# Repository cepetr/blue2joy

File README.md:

# 🕹️ Blue2Joy

**Blue2Joy** is an adapter that lets you use modern Bluetooth controllers with Atari 8-bit computers. It emulates **digital joysticks**, **analog paddles**, and supports **bidirectional communication** and much more. Try the live demo: https://cepetr.github.io/blue2joy/main.

While primarily intended for gamepads, the device is not limited to them - in principle, any BLE HID device, such as a keyboard or mouse, can be connected.

> Only devices that fully support the BLE HID over GATT Profile (HOGP) are supported. For this reason many older devices (especially gamepads) are unfortunately not usable with Blue2Joy. See [compatible devices](/doc/compatible-devices.md).

<div>

</div>

<div>

</div>

## Have a look at some demos:

## Use Cases
While there are other adapters that let Bluetooth controllers act as digital joysticks, Blue2Joy goes further. Besides standard and expected use cases, there are a few new possible ones that utilize analog input emulation or bidirectional communication:

- Use a gamepad as a digital joystick with up to 3 buttons (Joy2B+ standard)
- Use gamepad's analog sticks as paddles (direct or integration mode)
- Emulate paddles with a mouse
- Use a gamepad as an analog joystick (two axes on analog inputs) with up to 5 buttons
- Connect a mouse digitally- using quadrature encoding as on the Atari ST
- Connect a mouse in an analog way - using analog inputs for deltas, with up to 5 buttons
- Configure Blue2Joy via SPI-like communication over the joystick port
- Emulate the Y-axis of a light pen (conceptual idea, not sure if possible)
- Emulate an XEP80 terminal (work in progress)
- Send keycodes from the browser to Atari via paddle lines (used by the XEP80 terminal; requires [btjkbd.sys](/kbdrv/)).

Although designed for Atari 8-bit systems, Blue2Joy can be used with any device that follows the same joystick port pinout - with paddle functionality available only on Atari computers (see [details](/doc/paddle-emulation.md)).

## 🚧 Project Status

Blue2Joy is currently under active (but really slow) development. The hardware is stable and most of the core features have been successfully tested, but the software still needs some work to reach the level of polish I would consider complete.

## Repository Structure

This repository contains complete project documentation and source code for all Blue2Joy components shown in the following image.

### Blue2Joy Hardware
- Nordic nRF52840 (Cortex-M4F @ 64 MHz) with integrated Bluetooth 5 LE radio
- USB 2.0 Full-Speed (device mode only) for firmware updates, debugging, or use as a faster alternative to Bluetooth
- Female 9-pin D-sub connector
- RGB LED used as a status indicator (see [details](/doc/state-signalling.md))
- Two user push-buttons (see [details](/doc/button-functions.md))

For more details, see the [hardware](/hardware/) folder.

### Blue2Joy Firmware
- Supports pairing and connection to BLE HID devices (tested with Xbox Wireless Controller)
- Emulates a joystick port digital inputs as well as analog paddle potentiometers
- Supports bidirectional (SPI) communication with the Atari
- Indicates device status with an RGB LED
- Allows custom mapping of HID-device controls to joystick and paddle inputs
- Emulates an XEP80 terminal

For more details, see the [firmware](/firmware/) folder.

### Web Configuration
- A web application that allows you to configure the Blue2Joy device directly from any browser supporting the Web Bluetooth or Web USB standards
- Provides an easy way to configure the mapping of HID controls to joystick port digital and analog pins
- Allows you to configure the device even while it is connected to HID devices (e.g., gamepads, mice)
- Emulates an XEP80 terminal

The application is available at https://cepetr.github.io/blue2joy/main.

For more details, see the [webconfig](/webconfig/) folder.

### Atari Blue2Joy Keyboard driver
A driver for SpartaDOS that lets you use Blue2Joy as a keyboard. It can be used together with
XEP80 or on its own.

For more details, see the [atari](/atari/btjkbd) folder.

### Atari Blue2Joy Configuration Application
- Not implemented yet. This component currently exists only as a design intention.
- Intended to be an application that allows configuring the Blue2Joy device directly from Atari
- Planned to use the bidirectional (SPI-like) communication over the joystick port

For more details, see the [atari](/atari/btjmenu) folder.

## Feedback & Contributions

I'd be very happy to receive any feedback, pull requests, or even just a note that you've built and tried out Blue2Joy.

## License

This repository contains software, firmware, and hardware design files.

### Software and Firmware

All software and firmware files (in `atari/`, `firmware/` and `webconfig/`) are licensed under the GNU General Public License, version 3.

See [LICENSE-GPL](LICENSE-GPL) for details.

### Hardware

Schematics, PCB layout, mechanical design files (in `hardware/`) are licensed under the CERN Open Hardware Licence Version 2 - Strongly Reciprocal. You are free to use, modify, and share them, but if you distribute hardware or modified design files, you must also share your changes under the same license.

See [LICENSE-CERN](LICENSE-CERN) for details.

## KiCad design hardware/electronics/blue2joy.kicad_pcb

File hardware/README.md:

# 🔧 Blue2Joy — hardware

This folder contains the **KiCad** project and 3D design files for the Blue2Joy adapter:

* [`electronics/`](/hardware/electronics/) - KiCad project
* [`mechanical/`](/hardware/mechanical/) - 3-D model of the device’s enclosure

## Schematic & BOM

The design uses readily available SMD components and a XIAO nRF52840 module to keep the total cost and assembly complexity relatively low.

Schematic in PDF format is available [here](/hardware/electronics/fab_v1e/blue2joy-v1e.pdf)

The estimated parts cost is roughly USD 25, depending on the supplier and any volume discounts.

| # | Qty| Reference | Package |Part Numbers |
|----|---|-----------|---------|--------------------|
| 1  | 1 | U1 | | XIAO nRF52840 Plus |
| 2  | 1 | U2 | SOT-23-5 | TPS73133DBV |
| 3  | 2 | U3, U5 | SOT-23-6 | 74LVC2G17DBV |
| 4  | 3 | U4, U7, U8 | SOT-23-6 | 74LVC2G07DBV |
| 5  | 1 | U6 | SOT-23-5 | TLV9001IDBV |
| 6  | 1 | U9 | SOT-23-5 | XC8110AA01MR |
| 7  | 1 | U10 | SOT-23-6 | 74HCT2G34GV |
| 8  | 2 | Q1, Q3 | SOT-23-3 | BSS138 |
| 9  | 2 | Q4, Q5 | SOT-23-3 | SI2323DDS |
| 10 | 1 | J1 | - | DE9 Socket (Male)  |
| 11 | 2 | SW1, SW2 | - | OMRON B3FS-1010 |
| 12 | 1 | D1 | 2020 | WS2812-2020 |
| 13 | 8 | R1, R2, R3, R13, R14, R15, R18, R19 | 0805 | 10kΩ/125mW |
| 14 | 2 | R6, R10 | 0805 | 100kΩ/125mW |
| 15 | 4 | R8, R9, R11, R12 | 0805 | 18kΩ/125mW |
| 16 | 5 | R20, R21, R22, R23, R24 | 0805 | 820Ω/125mW |
| 17 | 2 | R4, R17 | 0805 | 1.8kΩ/125mW |
| 18 | 2 | R5, R16 | 0805 | 2.2kΩ/125mW |
| 19 | 4 | C1, C2, C3, C4 | 0805 | 1µF |
| 20 | 1 | C5 | 0805 | 10µF |
| 21 | 3 | C6, C7, C8 | 0805 | 100nF |

## PCB

The [`electronics/fab_v1d`](/hardware/electronics/fab_v1d/) folder contains the manufacturing files for the latest PCB revision.

## Assembly notes

Building the board **does require basic SMT soldering skills**.
If you have never worked with solder paste or hot air before, expect a small learning curve - nothing close to rocket science, but still a step up from through-hole work.

| Part type | Package | Difficulty (subjective) |
|-----------|---------|------------|
| Passives  | **0805** | easy; forgiving |
| Logic & power | **SOT-23-x** | fine for hot-air or drag solder, **be extra careful with orientation - SOT-23-6 parts have a tiny, barely visible dot marking pin 1** |
| MCU module | **XIAO nRF52840 Plus** (castellated) | can be hand-soldered with a fine-tip iron |
| RGB LED | **WS2812C-Mini** | the smallest part; watch orientation |

After assembly, verify that there are no shorts between pins on the SOT-23-x packages.

## DE9 Socket

DE9 (Cannon) connectors are manufactured only with a metal housing. After cutting along the edge, the plastic part can be popped out like a nut. However, the plastic parts differ between manufacturers, and in some cases, they need to be glued together.

## Hardware Status & Disclaimer

Although the device has been tested with three Atari models (800XL, 800XE, and 600XL - all PAL), hidden design flaws may still exist. Use all design files, instructions, and the board at your own risk; no warranties or guarantees are implied.

The plastic parts were printed from PLA (standard 0.4 mm nozzle, 0.2 mm layer height, 30% infill) on a Prusa Mk3 printer. The tolerances are quite tight, so it’s likely that on a different printer or with another material, there may be issues fitting the parts together.

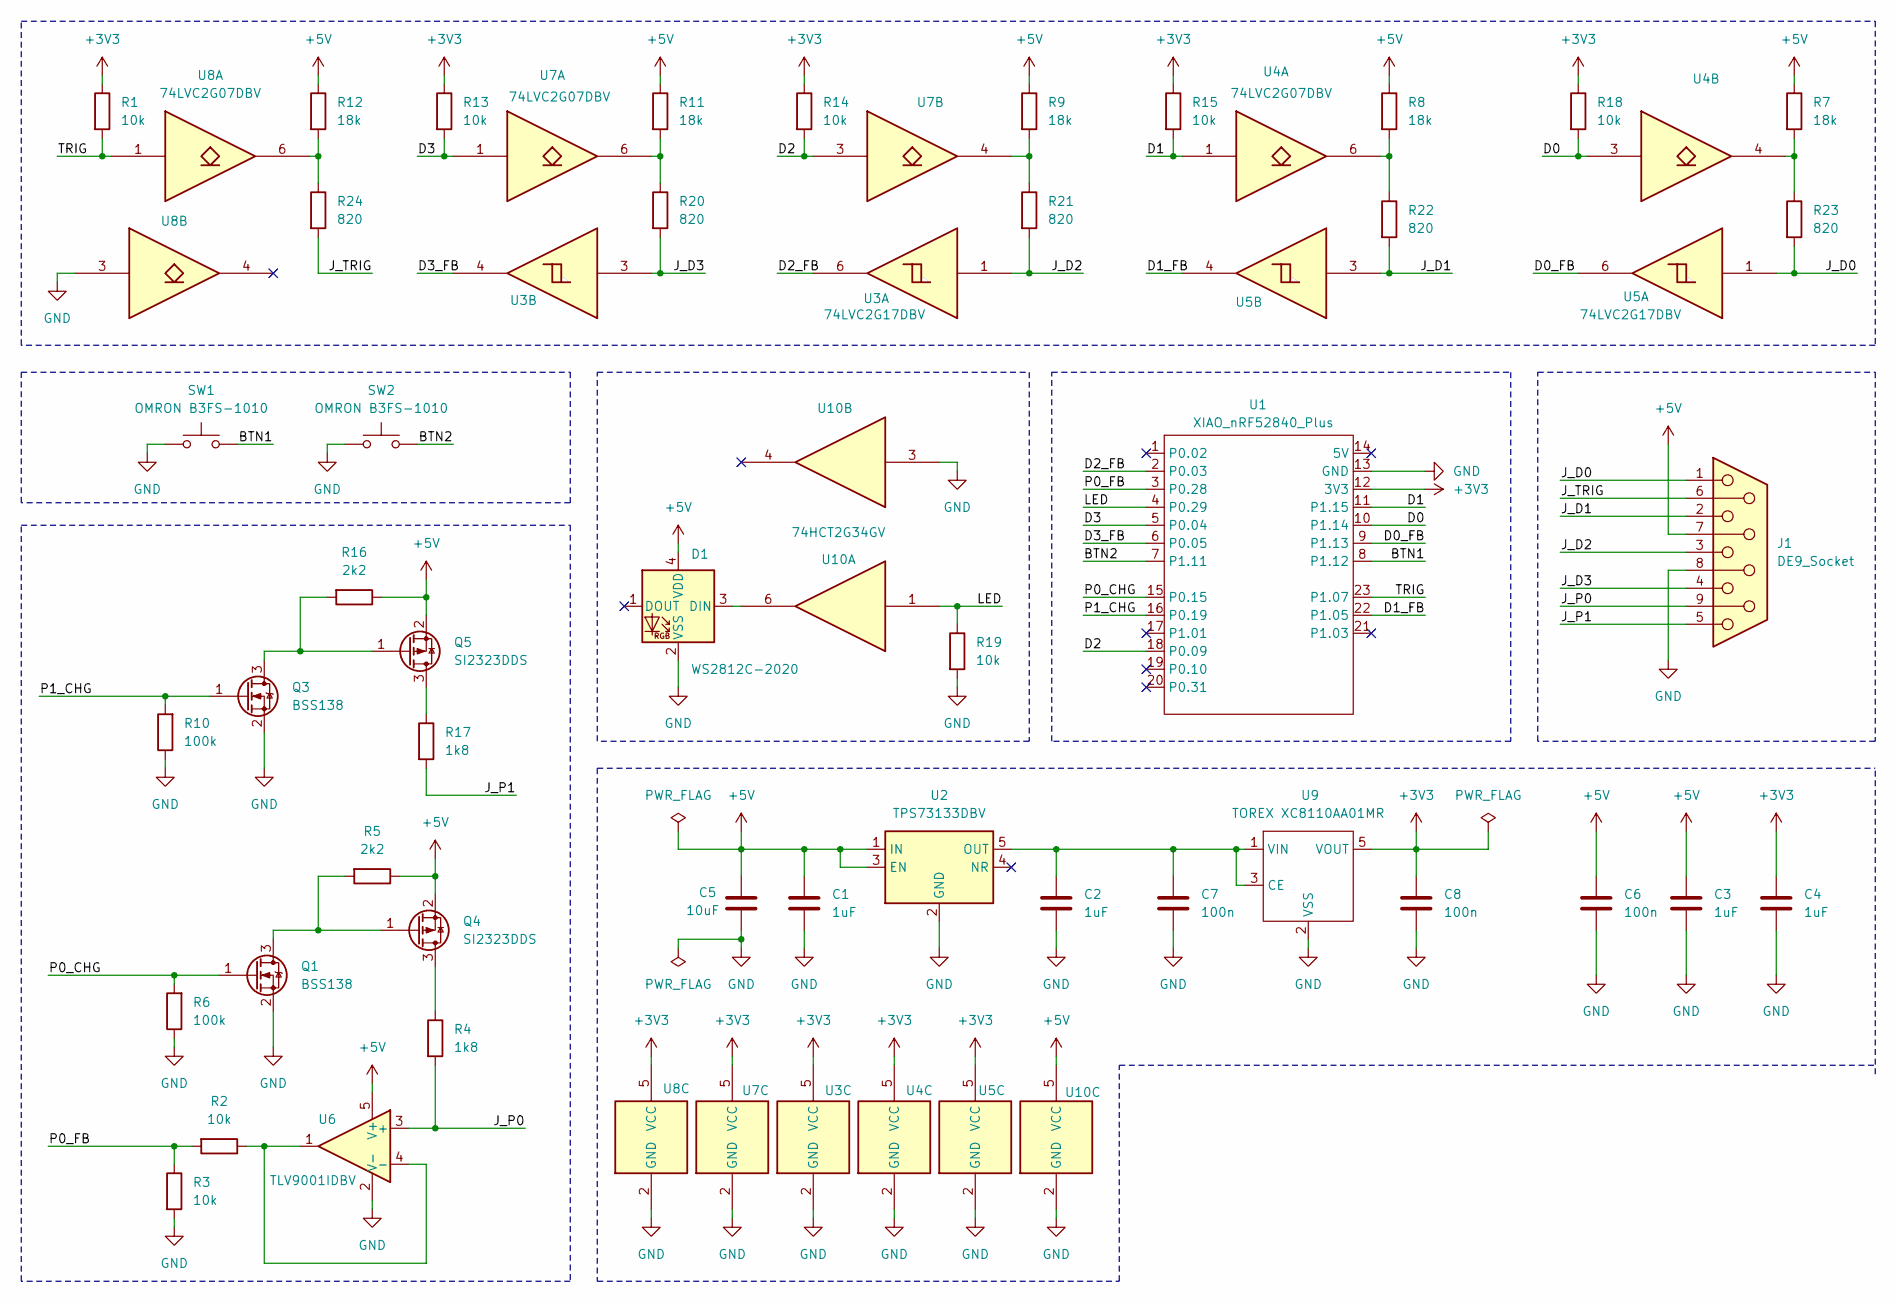
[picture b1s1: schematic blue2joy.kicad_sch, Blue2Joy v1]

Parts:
C1, C2, C3, C4: 1uF; C_0805_2012Metric
C5: 10uF; C_0805_2012Metric
C6, C7, C8: 100n; C_0805_2012Metric
D1: WS2812C-2020; LED_WS2812B-2020_PLCC4_2.0x2.0mm
J1: DE9_Socket; DSUB-9_Socket_EdgeMount_P2.77mm
Q1, Q3: BSS138; SOT-23
Q4, Q5: SI2323DDS; SOT-23
R1, R2, R3, R13, R14, R15, R18, R19: 10k; R_0805_2012Metric
R4, R17: 1k8; R_0805_2012Metric
R5, R16: 2k2; R_0805_2012Metric
R6, R10: 100k; R_0805_2012Metric
R7, R8, R9, R11, R12: 18k; R_0805_2012Metric
R20, R21, R22, R23, R24: 820; R_0805_2012Metric
SW1, SW2: OMRON B3FS-1010; SW_SPST_Omron_B3FS-100xP
U1: XIAO_nRF52840_Plus; XIAO-nRF52840-Plus-SMD
U2: TPS73133DBV; SOT-23-5
U3, U5: 74LVC2G17DBV; SOT-23-6
U4, U7, U8: 74LVC2G07DBV; SOT-23-6
U6: TLV9001IDBV; SOT-23-5
U9: TOREX XC8110AA01MR; SOT-23-5
U10: 74HCT2G34GV; SOT-23-6

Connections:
+3V3: C4.1, C8.1, R1.1, R13.1, R14.1, R15.1, R18.1, U1.12 (3V3), U3.5 (VCC), U4.5 (VCC), U5.5 (VCC), U7.5 (VCC), U8.5 (VCC), U9.5 (VOUT)
+5V: C1.1, C3.1, C5.1, C6.1, D1.4 (VDD), J1.7, Q4.2 (S), Q5.2 (S), R5.1, R7.1, R8.1, R9.1, R11.1, R12.1, R16.1, U2.1 (IN), U2.3 (EN), U6.5 (V+), U10.5 (VCC)
/BTN1: SW1.1, U1.8 (P1.12)
/BTN2: SW2.2, U1.7 (P1.11)
/D0: R18.2, U1.10 (P1.14), U4.3
/D0_FB: U1.9 (P1.13), U5.6
/D1: R15.2, U1.11 (P1.15), U4.1
/D1_FB: U1.22 (P1.05), U5.4
/D2: R14.2, U1.18 (P0.09), U7.3
/D2_FB: U1.2 (P0.03), U3.6
/D3: R13.2, U1.5 (P0.04), U7.1
/D3_FB: U1.6 (P0.05), U3.4
/J_D0: J1.1, R23.2, U5.1
/J_D1: J1.2, R22.2, U5.3
/J_D2: J1.3, R21.2, U3.1
/J_D3: J1.4, R20.2, U3.3
/J_P0: J1.9, R4.2, U6.3 (+)
/J_P1: J1.5, R17.2
/J_TRIG: J1.6, R24.2
/LED: R19.1, U1.4 (P0.29), U10.1
/P0_CHG: Q1.1 (G), R6.2, U1.15 (P0.15)
/P0_FB: R2.2, R3.1, U1.3 (P0.28)
/P1_CHG: Q3.1 (G), R10.2, U1.16 (P0.19)
/TRIG: R1.2, U1.23 (P1.07), U8.1
GND: C1.2, C2.2, C3.2, C4.2, C5.2, C6.2, C7.2, C8.2, D1.2 (VSS), J1.8, Q1.2 (S), Q3.2 (S), R3.2, R6.1, R10.1, R19.2, SW1.2, SW2.1, U1.13 (GND), U2.2 (GND), U3.2 (GND), U4.2 (GND), U5.2 (GND), U6.2 (V-), U7.2 (GND), U8.2 (GND), U8.3, U9.2 (VSS), U10.2 (GND), U10.3
unnamed: D1.3 (DIN), U10.6
unnamed: Q1.3 (D), Q4.1 (G), R5.2
unnamed: Q3.3 (D), Q5.1 (G), R16.2
unnamed: Q4.3 (D), R4.1
unnamed: Q5.3 (D), R17.1
unnamed: R11.2, R20.1, U7.6
unnamed: R12.2, R24.1, U8.6
unnamed: R9.2, R21.1, U7.4
unnamed: R8.2, R22.1, U4.6
unnamed: R7.2, R23.1, U4.4
unnamed: C2.1, C7.1, U2.5 (OUT), U9.1 (VIN), U9.3 (CE)
unnamed: R2.1, U6.1, U6.4 (-)

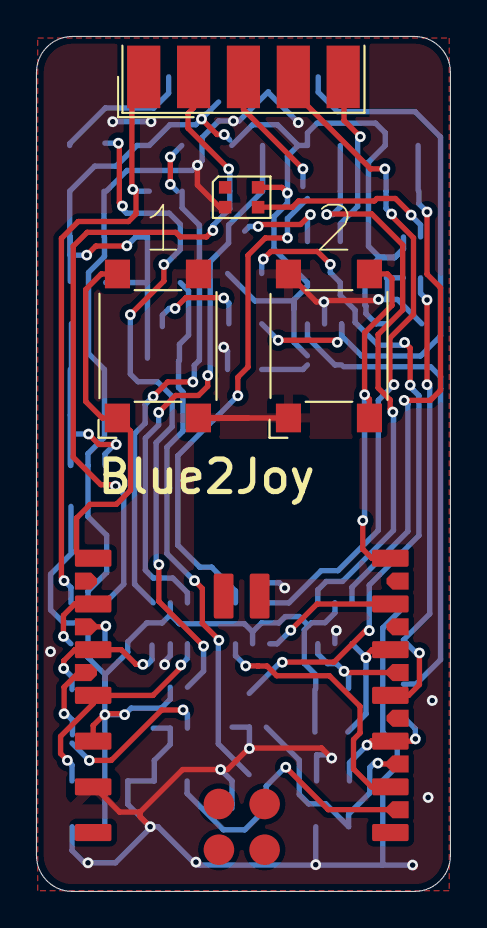
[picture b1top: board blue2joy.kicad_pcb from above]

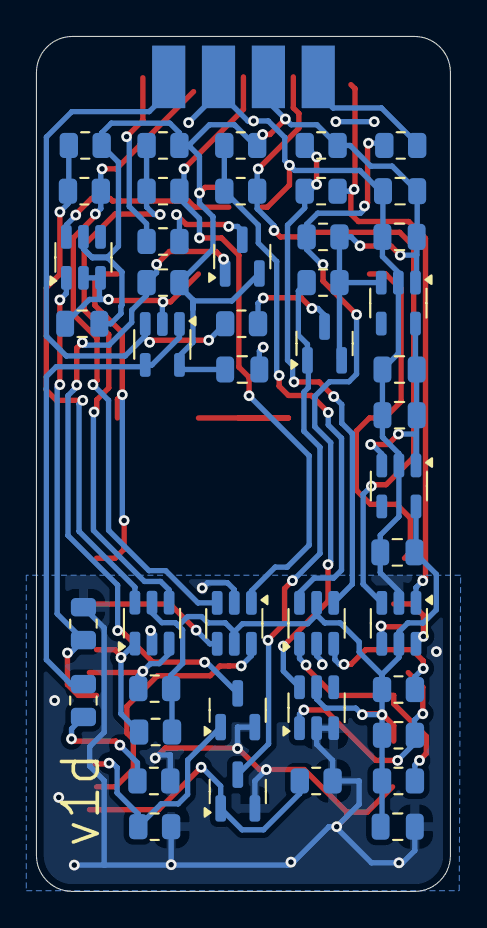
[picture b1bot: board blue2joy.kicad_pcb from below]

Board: 2 copper layers, 23.0 x 47.5 mm, 50 parts (45 on the bottom side), 37 nets.

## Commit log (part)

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2025-10-25 remove bonded flag
2025-10-25 show connection state string
2025-10-25 fix scan dialog button
2025-10-25 fix txq_ready flag handling
2025-10-25 Add profile change, device delete
2025-10-25 Add connect button
2025-10-25 add hatSwitch, intSpeed configuration
2025-10-25 fix fixed profile
2025-10-25 fix code formatting
2025-10-25 update todo
2025-10-25 reorganize files
2025-10-25 add sidebar nav
2025-10-25 group pins and pots
2025-10-26 replace picocss with bootstrap
2025-10-26 refactor pin and pot editors
2025-10-26 remove unnecessary comments
2025-10-26 one line editors
2025-10-26 pin/pot header of the left
2025-10-26 simplify pin/pot editors
2025-10-26 add Not Assigned usage
2025-10-26 improve pot editor
2025-10-28 detect disconnected device
2025-10-28 update todos
2025-10-28 add start/stop advertising button
2025-10-28 refactor btsvc, make is_advertising atomic
2025-10-28 add advertising timeout
2025-10-28 center home screen
2025-10-28 update 3d files
2025-10-30 configure rc oscillator calibration
2025-10-30 estimate pot scanning period
2025-10-30 minor doc updates
2025-11-15 centralize device scanning logic in BtjModel
2025-11-15 improve error handling
2025-11-15 add list of compatible devices
2026-01-10 improve navigation, add offcanvas menu
2026-01-10 improve pin/pot editor layout
2026-01-10 subscribe to the first report in the report map
2026-01-10 update the list of compatible devices
2026-01-10 discover report characteristics properly
2026-01-11 update doc
2026-01-11 Deploy webconfig for refs/heads/dev 83e64820c5a60210d097cd2bc1a51690986f0b69
2026-01-11 Deploy webconfig for refs/heads/main 7cfd7e5f635778ab4421fdfd35b870682fe4e947
2026-01-11 Deploy webconfig for refs/tags/v0.1 7cfd7e5f635778ab4421fdfd35b870682fe4e947
2026-01-11 Deploy webconfig for refs/heads/dev f3997a750e14e0e93c379cd23fa59fcdc3536843
2026-01-11 Deploy webconfig for refs/heads/dev de0f1742ecac871c870539c2e86fbb9555068cc0
2026-01-11 fix routing when using version prefix
2026-01-17 use constants for pot min/max values
2026-01-17 improve mapper, introduce integrators, analog encoders
2026-01-17 reconfigure io pins if the active profile is modified
2026-01-18 fix hid usage selector
2026-01-18 update documentation
2026-01-20 improve responsiveness on smaller screens
2026-01-20 improve html formatting
2026-01-21 implement event handler as arrow functions
2026-01-21 use hash based routing
2026-01-22 decrease padding and margin in editor cards
2026-01-23 refactor filtering logic in hid-usage-select
2026-01-23 indicate the device state using icons
2026-01-24 Deploy webconfig for refs/heads/main c044f10ed8133ad798e0c5b402b8f7d3912fa732
2026-01-24 docs: introduce new todo list
2026-01-24 display digital I/O and potentiometer states in web UI
2026-01-24 Deploy webconfig for refs/heads/main 1341ea238d3ab0ff4edbc8877fbeef8f62b088e6
2026-01-24 fix: close off-canvas navbar on menu item selection
2026-01-24 Deploy webconfig for refs/heads/main 8b34d09968044fce412b47f3ab97f2809fad9546
2026-01-24 Deploy webconfig for refs/tags/v0.2 fdede7f2eb40641e44b04d57845cf0318c1d1324
2026-01-24 fix: change navbar to fixed position
2026-01-25 fix: update pot outputs when mapped to integrators
2026-01-25 feat: improve pot accuracy and decrease jitter
2026-01-26 docs: add link to youtube video
2026-02-07 Deploy webconfig for refs/heads/dev 37e24393fac06f7e3561e95dac261e45ec6e61c9
2026-02-15 Deploy webconfig for refs/heads/dev d2f2fb405a16679e680dbffca6a3e6028b5e1cf0
2026-02-15 Deploy webconfig for refs/heads/dev 2f0d46f78eb7f1efc6667cf7629ddd15d8cb884f
2026-02-16 refactor: introduce joy_port module
2026-02-22 Deploy webconfig for refs/heads/dev adc2743a07af16aeb9920ea52470f24ef194586f
2026-02-28 fix: get rid of compiler warning
2026-02-28 feat: add initial XEP80 support
2026-02-28 fix: correct minor typos in README files
2026-02-28 Deploy webconfig for refs/heads/main 8958d61f0d9b71b379b32a0a68bb964f12864f6a
2026-04-25 feat: refactor serialization methods and add BinaryReader/Writer
2026-04-25 chore: use code prettier
2026-04-25 feat: improve payload length validation
2026-04-25 fix: minor fixes
2026-04-25 Deploy webconfig for refs/heads/main 91f02ef711e26d9645d4395050d547117573d5c6
2026-04-25 fix: handle case when no HID report characteristics are discovered
2026-04-25 fix: correct attribute length validation in btjp_rxq_write
2026-04-25 fix: improve HID advertisement validation
2026-04-25 fix: fix report characteristic search
2026-04-25 fix: refactor connection handling to address synchronization issues
2026-04-25 fix: fix minor issues in btjp
2026-04-25 fix: fix possible deadlocks in devmgr
2026-04-25 fix: fix joy_port_get_state
2026-04-25 fix: initialized rgbled mutex
2026-04-25 refactor: advance xep80 tx queue on PWM stopped event
2026-04-25 Deploy webconfig for refs/heads/dev d8c77efcc19be45625e430619cb513d16f0a93d7
2026-04-25 feat: light/dark themes
2026-04-25 Deploy webconfig for refs/heads/dev 44a1043dc416b9ff9fb84442d8b0fc764673ac68
2026-04-25 fix: preserve device order when importing settings
2026-04-26 feat: generalize btj-transport
2026-04-26 fix: fix device state update
2026-04-26 feat: demo mode
2026-04-26 Deploy webconfig for refs/heads/dev 728198aa8a3deee30e3d466f059dadbb69a29296
2026-04-26 docs: added changelog
2026-04-26 chore: bump version to 0.3.0
2026-04-26 feat: add webusb device
2026-04-26 fix: add missing compileCommands setting in VSCode config
2026-04-26 feat: add webusb transport
2026-05-24 feat: add usbsvc
2026-05-24 refactor: enable shell, use logging modules
2026-05-24 docs: update changelog
2026-05-24 chore: cump version to 0.4.0
2026-05-24 Deploy webconfig for refs/heads/main f593613bee865fda0e75711fc0501726cdad7873
2026-05-24 Deploy webconfig for refs/heads/dev b1d4bfcf371e771b46008c79d088b1f3f9600cf6
2026-05-24 Deploy webconfig for refs/heads/dev b7d9e30aaf94e5c20f3043194f6708d6f3947c6f
2026-05-24 Deploy webconfig for refs/heads/dev 063e3f3b09e004f13898c73395ac229c33302266
2026-05-24 Deploy webconfig for refs/heads/main 063e3f3b09e004f13898c73395ac229c33302266
2026-05-25 fix: improve atascii to unicode mapping
2026-05-30 fix: fix raise conditions in webusb
2026-05-30 fix(core): remove unnecessary synchronization
2026-05-30 fix: usbsvc state synchronization
2026-05-30 fix: persist XEP80 render mode and color selection
2026-05-30 Deploy webconfig for refs/heads/dev cea36d1e9b7c1bfb536d2e10016f84330abcfbee
2026-05-30 feat: improve logging of connection errors
2026-05-30 fix: alternating webusb reconnect timeouts
2026-05-30 fix: procesing of 0x9B in xep80 escape mode
2026-05-30 fix: hiding toolbox in fullscreen mode
2026-05-30 Deploy webconfig for refs/heads/dev bce2f2396422f736518d6a4bed1ad344fa2a57fd
2026-05-31 Deploy webconfig for refs/heads/main dc8b556241330081b8ca45b15df35b60c906c580
2026-05-31 fix: bundle mono space font
2026-05-31 Deploy webconfig for refs/heads/main a7738bb909d7e7897df81cc81ed2cda134115ffa
2026-05-31 docs: updte readme, add link to xep80 video
2026-05-31 chore: bump version to 0.5
2026-06-01 fix: render wide chars and cursor correctly
2026-06-01 Deploy webconfig for refs/heads/dev 3463d40e51efbc934161310a6584a54616f75636
2026-06-04 feat: add MS OS 2.0 WinUSB BOS descriptors for Windows
2026-06-04 chore: bump version to 0.5.1
2026-06-04 Deploy webconfig for refs/heads/main d077587c18177c0474979c257a8b84b11b086d45
2026-06-05 chore(web): remove unused variable
2026-06-05 Deploy webconfig for refs/heads/dev c78e3b0cb10dc2484016b259fef5742a14394c45
2026-06-05 Deploy webconfig for refs/heads/dev 60979df86a10f7d0b9fab8aaecd61c2bbd2650c8
2026-06-05 feat(web): improve connection panel wording and alignment
2026-06-05 fix(web): use theme colors for xep80 activation card
2026-06-05 Deploy webconfig for refs/heads/dev 4672bb892cd5dc2deb17539baad30817a635e606
2026-06-05 feat(web): improve error state UI and reconnect flow
2026-06-05 Deploy webconfig for refs/heads/main 185c8acfb45daa0bfeaa9d092feb95ebf1670bf5
2026-06-05 fix(firmware): correctly handle character deletion in a line
2026-06-05 feat(firmware): handle xep80 cursor commands
2026-06-05 feat(firmware): support baudrate updates - wip
2026-06-05 fix(web): correct inverted attribute handling for normal/international fonts
2026-06-06 refactor(web): move XEP80 color constants to palette
2026-06-06 refactor(web): factor out xep80 rle decoder
2026-06-06 refactor(web): extract XEP80 register parsing to xep80-regs
2026-06-06 refactor(web): split XEP80 renderer into text and bitmap modules
2026-06-06 chore(web): move all xep80 related files to xep80 folder
2026-06-06 refactor(web): factored out xep80-toolbox
2026-06-06 refactor(web): factor out xep80-text and xep80-bitmap views
2026-06-06 refactor(web): introduce frame controller
2026-06-06 refactor(web): extract xep80 overlay prompts
2026-06-06 refactor(web): make xep80-toolbox the XEP80 config provider
2026-06-06 refactor(xep80): colocate constants with XEP80 components
2026-06-06 chore(web): rename FrameBuffer to Frame
2026-06-06 feat(web): modernize xep80 toolbox
2026-06-06 Deploy webconfig for refs/heads/dev 57e9085578eb371385b47b7bd94a008286d7511a
2026-06-06 Deploy webconfig for refs/heads/dev 21495787bec61b7f7c40553ac1c77b45e98bf0b6
2026-06-06 Deploy webconfig for refs/heads/main 6b5ac7fd491375af0e9a51b03b10f7c032cf9387
2026-06-06 Deploy webconfig for refs/heads/dev 2e14f0071cc11fe5dd41c1656e602f105a90744c
2026-06-06 Deploy webconfig for refs/heads/dev f138271b8af2261243bb11e0c507749b0b5d49a7
2026-06-06 perf(web): reduce xep80 bitmap render overhead
2026-06-06 feat(web): enable antialiasing when drawing original glyphs
2026-06-06 Deploy webconfig for refs/heads/main 0ce397910d53c9e66128ada9af9e406bfa8ca0a8
2026-06-06 chore(web): rename transports
2026-06-06 refactor(web): extract connect-view component from app-root
2026-06-06 feat(web): use icons instad of buttons in navbar
2026-06-06 feat(web): improve navbar behavior
2026-06-06 feat(web): hid xep80 toolbar when xep80 not active
2026-06-06 feat(web): improve icons/buttons in device-view
2026-06-06 feat(web): align connect buttons
2026-06-06 fix(web): fit xep80 text view on small screens
2026-06-06 Deploy webconfig for refs/heads/dev cd5e5ad759d71cef3221bafc0ed2cdc5e5fdeaa4
2026-06-07 chore(all): add vscode workspace
2026-06-08 docs: remove TODOs
2026-06-08 Deploy webconfig for refs/heads/dev 73616b21ebe71b40d7f1fd073c6a5b878775fca1
2026-06-10 fix(firmware): fix missed updates before synced offset
2026-06-10 Deploy webconfig for refs/heads/main 8528b0fcf58b42ee617ba45f9fd6cdaa01a3a64d
2026-06-13 Deploy webconfig for refs/heads/dev 25b5164533dc46a2c827ad6500caef6ed60343c2
2026-06-14 Deploy webconfig for refs/heads/dev 2915dd4630ea6da5698c95fc5b0c43394acc8b07
2026-06-14 feat(firmware): send keypresses via pot inputs
2026-06-14 Deploy webconfig for refs/heads/dev 111d9dadc93305a3cd18eabc963a8518dd19d47c
2026-06-14 Deploy webconfig for refs/heads/dev d04aa3b9f4cba9b4626dc222d3f698868ce28ad0
2026-06-15 feat(web): improve btj connection logging
2026-06-15 fix(web): clear advertised devices before scanning
2026-06-15 feat(firmware): improve ble conn logging
2026-06-15 fix(firmware): suppress unhandled event log for EV_SUBJECT_CONN_ERROR
2026-06-15 fix(firmware): defer device entry creation until address resolution
2026-06-15 fix(web): copy only current BLE notification payload bytes
2026-06-15 chore(firmware): reorganize atari folder
2026-06-15 fix(firmware): track report_ref reads by index in device struct
2026-06-15 fix(firmware): enforce HID discovery order (report map -> descriptors -> report_ref)
2026-06-15 fix(firmware): fix OOB read in single-element LED sequences
2026-06-15 chore(firmware): bump version to 0.6.0
2026-06-15 Deploy webconfig for refs/tags/v0.6 32cdd59c58d732128bfbaf4baef3387203815314
2026-06-15 Deploy webconfig for refs/heads/main 32cdd59c58d732128bfbaf4baef3387203815314
